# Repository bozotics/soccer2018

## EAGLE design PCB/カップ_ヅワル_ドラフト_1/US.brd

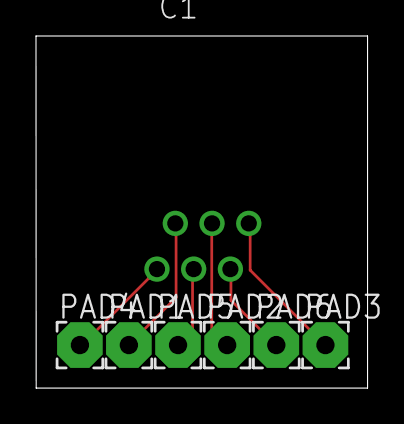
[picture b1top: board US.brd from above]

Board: 2 copper layers, 18.4 x 19.6 mm, 7 parts (0 on the bottom side), 6 nets.

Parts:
C1: 6P6C_FEMALE
PAD1, PAD2, PAD3, PAD4, PAD5, PAD6: 2,54/1,0

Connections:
unnamed: C1.1, PAD1.1
unnamed: C1.2, PAD2.1
unnamed: C1.3, PAD3.1
unnamed: C1.4, PAD4.1
unnamed: C1.5, PAD5.1
unnamed: C1.6, PAD6.1
